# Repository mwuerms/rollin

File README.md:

# rollin
a self balancing robot, "rolling around"

## Test 1

quick prototyp for using MPU9250 to get acc x, y values and gyro z values (change rate in deg/s !) to calculate present angle:

 +   0° is upright
 + -90° fall over foreward
 +  90° fall over backwards

## Better Serial Plotter

A very nice serial plotter tool (win, mac, linux), using space ' ' or tabs '\t' as value separator.

https://github.com/nathandunk/BetterSerialPlotter#example-arduino-code

Thank you nathandunk (https://github.com/nathandunk)

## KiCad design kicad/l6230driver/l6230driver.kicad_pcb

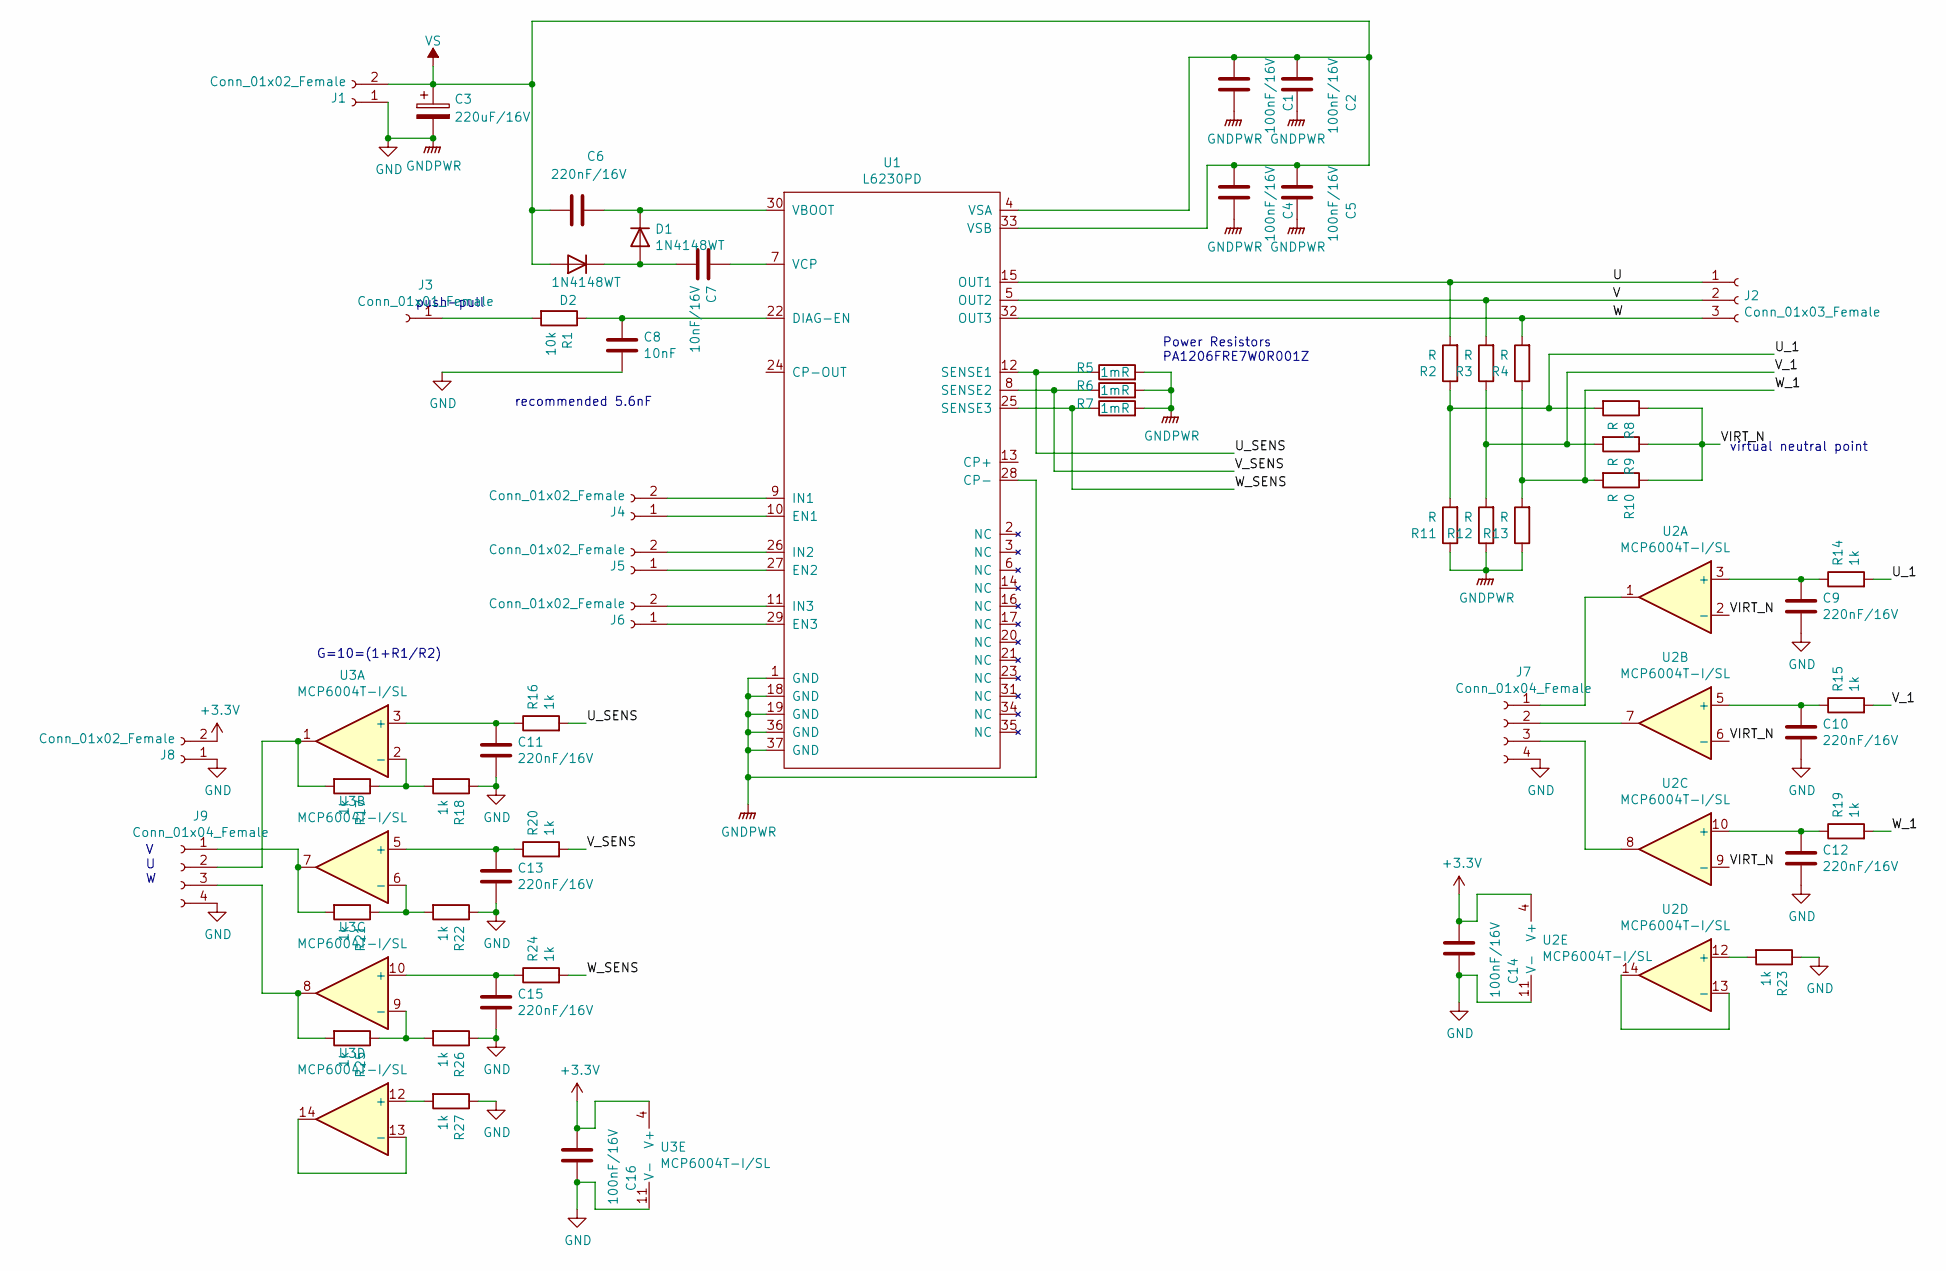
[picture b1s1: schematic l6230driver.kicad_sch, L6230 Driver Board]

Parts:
C1, C2, C4, C5, C14, C16: 100nF/16V; C_0603_1608Metric
C3: 220uF/16V; CP_Radial_D8.0mm_P2.50mm
C6, C9, C10, C11, C12, C13, C15: 220nF/16V; C_0603_1608Metric
C7: 10nF/16V; C_0603_1608Metric
C8: 10nF; C_0603_1608Metric
D1, D2: 1N4148WT; D_SOD-523
J1, J4, J5, J6, J8: Conn_01x02_Female; PinSocket_1x02_P2.54mm_Vertical
J2: Conn_01x03_Female; PinSocket_1x03_P2.54mm_Vertical
J3: Conn_01x01_Female; PinSocket_1x01_P2.54mm_Vertical
J7, J9: Conn_01x04_Female; PinSocket_1x04_P2.54mm_Vertical
R1: 10k; R_0603_1608Metric
R2, R3, R4, R8, R9, R10, R11, R12, R13: R; R_0603_1608Metric
R5, R6, R7: 1mR; R_1206_3216Metric
R14, R15, R16, R17, R18, R19, R20, R21, R22, R23, R24, R25, R26, R27: 1k; R_0603_1608Metric
U1: L6230PD; HSOP-36
U2, U3: MCP6004T-I/SL; SOIC-14_3.9x8.7mm_P1.27mm

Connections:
+3V3: C14.2, C16.2, J8.2, U2.4 (V+), U3.4 (V+)
/U: J2.1, R2.2, U1.15 (OUT1)
/U_1: R2.1, R8.2, R11.2, R14.2
/U_SENS: R5.1, R16.2, U1.12 (SENSE1)
/V: J2.2, R3.2, U1.5 (OUT2)
/VIRT_N: R8.1, R9.1, R10.1, U2.2 (-), U2.6 (-), U2.9 (-)
/V_1: R3.1, R9.2, R12.2, R15.2
/V_SENS: R6.1, R20.2, U1.8 (SENSE2)
/W: J2.3, R4.2, U1.32 (OUT3)
/W_1: R4.1, R10.2, R13.2, R19.2
/W_SENS: R7.1, R24.2, U1.25 (SENSE3)
GND: C1.1, C2.1, C3.2, C4.1, C5.1, C8.2, C9.2, C10.2, C11.2, C12.2, C13.2, C14.1, C15.2, C16.1, J1.1, J7.4, J8.1, J9.4, R5.2, R6.2, R7.2, R11.1, R12.1, R13.1, R18.1, R22.1, R23.1, R26.1, R27.1, U1.1 (GND), U1.18 (GND), U1.19 (GND), U1.28 (CP-), U1.36 (GND), U1.37 (GND), U2.11 (V-), U3.11 (V-)
unnamed: C6.1, D1.1 (K), U1.30 (VBOOT)
unnamed: C7.1, U1.7 (VCP)
unnamed: C7.2, D1.2 (A), D2.1 (K)
unnamed: C8.1, R1.1, U1.22 (DIAG-EN)
unnamed: C9.1, R14.1, U2.3 (+)
unnamed: C10.1, R15.1, U2.5 (+)
unnamed: C11.1, R16.1, U3.3 (+)
unnamed: C12.1, R19.1, U2.10 (+)
unnamed: C13.1, R20.1, U3.5 (+)
unnamed: C15.1, R24.1, U3.10 (+)
unnamed: J3.1, R1.2
unnamed: J4.1, U1.10 (EN1)
unnamed: J4.2, U1.9 (IN1)
unnamed: J5.1, U1.27 (EN2)
unnamed: J5.2, U1.26 (IN2)
unnamed: J6.1, U1.29 (EN3)
unnamed: J6.2, U1.11 (IN3)
unnamed: J7.1, U2.1
unnamed: J7.2, U2.7
unnamed: J7.3, U2.8
unnamed: J9.3, R25.2, U3.8
unnamed: R17.1, R18.2, U3.2 (-)
unnamed: J9.2, R17.2, U3.1
unnamed: R21.1, R22.2, U3.6 (-)
unnamed: J9.1, R21.2, U3.7
unnamed: R23.2, U2.12 (+)
unnamed: R25.1, R26.2, U3.9 (-)
unnamed: R27.2, U3.12 (+)
unnamed: U2.13 (-), U2.14
unnamed: U3.13 (-), U3.14
VS: C1.2, C2.2, C3.1, C4.2, C5.2, C6.2, D2.2 (A), J1.2, U1.4 (VSA), U1.33 (VSB)

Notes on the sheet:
V U W
push-pull
recommended 5.6nF
virtual neutral point
Power Resistors PA1206FRE7W0R001Z
G=10=(1+R1/R2)

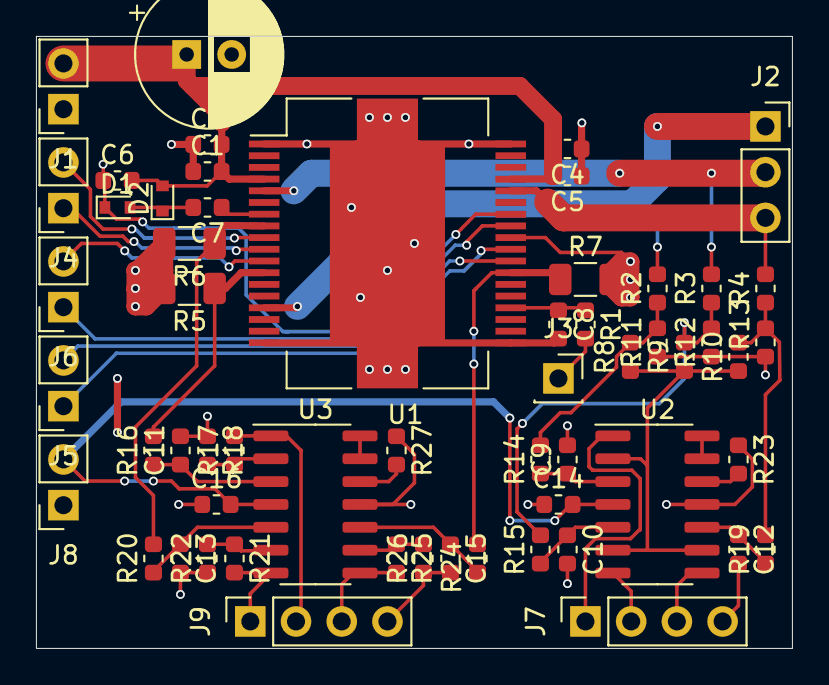
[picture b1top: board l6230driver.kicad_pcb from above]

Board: 2 copper layers, 42.0 x 34.0 mm, 57 parts (0 on the bottom side), 43 nets.

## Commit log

2022-09-09 added stand to test mpu9250
2022-09-09 added 1st testing routines to get familiar with mpu9250 all included in main.c, so project can be regenerated from test1.ioc using STM32CubeIDE
2022-09-10 mpu9250: more testing: found a complementary filter to get a reasonable angle from acc + gyro
2022-09-11 started rollinBalancer, implemented functions from test1
2022-09-13 validated angle_deg
2022-09-14 started with r1 (1st version of cad) but I cannot continue, parts have not arrived yet
2022-09-16 copied from project pwmgen
2022-09-16 sucessfully found mpu650 on addr 208 (8 bit incl R/W)
2022-09-16 i2c routines
2022-09-16 added string_buffer from rollinBalancer
2022-09-17 1st bldc test: woohoo some movement, but no rotation :-(
2022-09-17 2nd attempt: this motor runs, actually quite fast
    using lookuptable sine[96], update every 8 timer1 interrupts = 144us ->
    turns at approx. 11 revolutions / s
2022-09-18 teststand created to mount motor + mpu6500
2022-09-18 mpu6500 i2c sucessful communication
2022-09-18 mpu6500 set to active: works
2022-09-19 angle calculation: works
2022-09-22 pid started
2022-09-24 r1: motor speed in motor.c
2022-09-24 start r01 using FlyCat 2204 Gimbal BLDC
2022-09-26 added nunchuck to rollin r1
2022-09-27 Makefile added reset to start bootloader and do nothing
2022-09-27 added scale to pwm (to scale torque) but do not use
2022-09-28 use motor to generate accurate timeout from TIMER0_OVF
2022-09-28 started PID tuneing
2022-09-28 change periode from 256 (62500 Hz) to 16 (1 MHz), so current does not go into saturation
2022-10-05 torque measurement of flycat 2204 motors: WAY TOO WEAK for this application
    I cannot proceed this way, I have to use more powerfull motors!
2022-10-05 kicad started L6230 driver board
2022-10-05 started pcb
2022-10-08 schematics + placing
2022-10-09 added HSOP-36 footprint to own pritty-lib, placing, routing
2022-10-09 100% routed
2022-10-11 export to order, added zip with gerber + drill
2022-10-14 r02 started using 5010 gimbal bldc
2022-10-14 printing r02 test stand and arm
2022-10-16 added motor holder v1.0, including as5600 pcb
2022-10-21 export brd + schematics
2022-10-26 migrated to 6.6.1
2022-10-31 added as5600 angle sensor
2022-11-09 upgraded to CubeIde 1.10, I2C LL, reading as5600 angles work
2024-08-30 started r03 from r02
    added m3_cut and m3_nut_bolt_cut
2024-08-31 rav a of parts _1, _2, _3
2024-08-31 rev b for parts _1, _2, _3
2024-09-01 _1b minor adjustments, angles and nut dia
2024-09-10 new mpuholder stand
2024-09-10 removed as5600 and therefore i2c
    also use str_buf functions from mmlib
2024-09-10 changed peripherials
    removed i2c1, usb
    added usart1, adc1 in8, in9
2024-09-10 started rollin_ctrl
2024-09-11 sending data on uart: works
2024-10-24 rollinBalancer stop here
2024-10-24 rollinL412 started
2024-10-24 added modules
2025-05-14 rollin_ctrl started FOC
2025-05-14 rollin_ctrl use TIM3 to ctrl speed
2025-06-29 r04 started
2025-06-29 r04test_v1.1 added
2025-06-29 many changes to the code
2025-07-02 rollin2: started an other try
2025-07-02 changed i2c from LL to HAL, now reading as5600 is working
2025-07-02 added HAL files
2025-07-02 rollin2 all coded, ready to test speed control
2025-07-05 started logging
2025-07-06 rollin2 tested "bldc_motor_velocity_openloop()": OK, tested up to 7 rot/s
2025-07-06 rollin2: suing calcs_sinf_from_lut() tested: OK
2025-07-06 rollin2 openloop angle control, tested: OK
